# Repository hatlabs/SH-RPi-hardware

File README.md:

# Sailor Hat for Raspberry Pi (SH-RPi)

## Introduction

The Sailor Hat for Raspberry Pi (SH-RPi) is a versatile power management board designed for the Raspberry Pi and similar single-board computers. With the SH-RPi connected, you can create deeply integrated servers that shut down safely when power is turned off and wake up automatically when power is restored.

SH-RPi supports all Raspberry Pi models with a 40-pin GPIO header (every model since the Pi 1 Model B+). Additionally, it is compatible with Raspberry Pi Compute Module 4 boards and other single-board computers that have a 40-pin Raspberry Pi-compatible GPIO header or an external I2C interface with a 5V power input.

The [documentation site](https://docs.hatlabs.fi/sh-rpi/) has details on the hardware and software features of the board.

This repository contains the KiCad hardware design files for Sailor Hat.
There are two other related repositories: 
[firmware](https://github.com/hatlabs/SH-RPi-firmware) and 
[daemon](https://github.com/hatlabs/SH-RPi-daemon).

The documentation site is at [docs.hatlabs.fi/sh-rpi](https://docs.hatlabs.fi/). The devices are available for purchase at [shop.hatlabs.fi](https://shop.hatlabs.fi).

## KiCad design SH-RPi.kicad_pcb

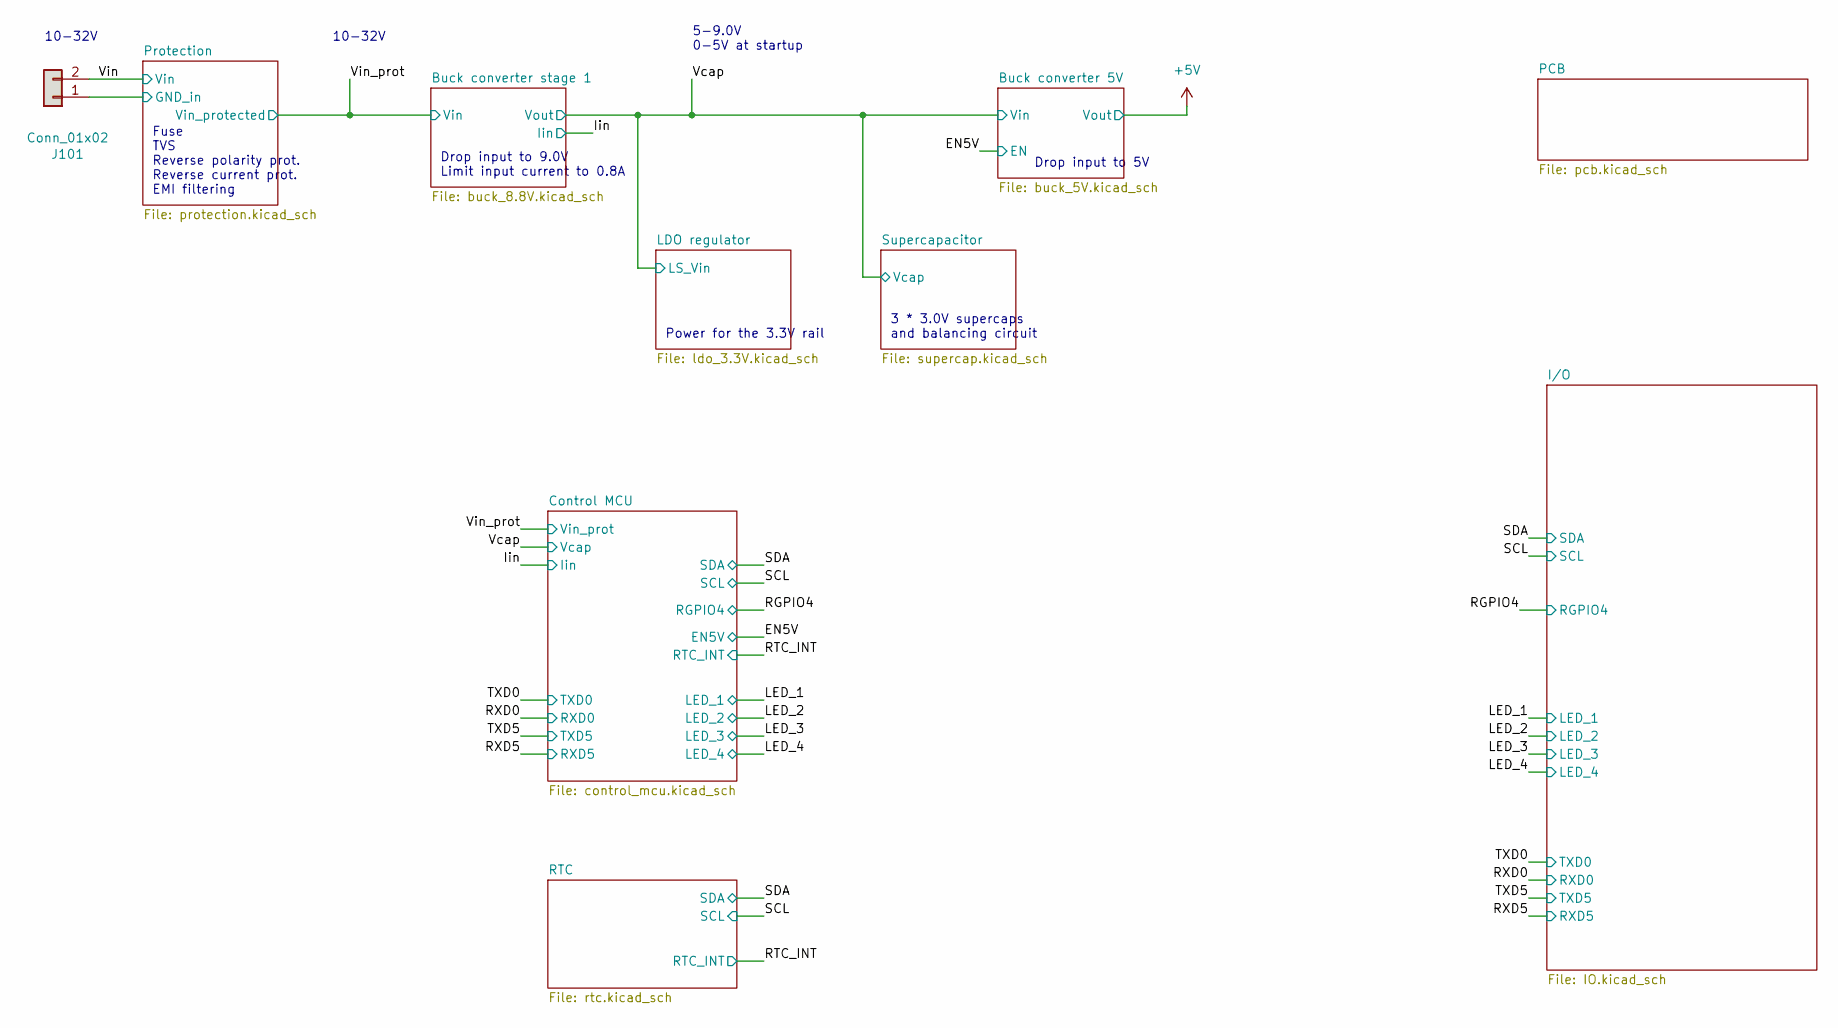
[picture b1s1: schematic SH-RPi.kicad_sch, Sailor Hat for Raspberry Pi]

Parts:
J101: Conn_01x02; PhoenixContact_MC_1,5_2-G-3.81_1x02_P3.81mm_Horizontal; LCSC C8387

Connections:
/Protection/GND_in: J101.1; also elsewhere on the board
/Vin: J101.2; also elsewhere on the board

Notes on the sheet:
Power for the 3.3V rail
Drop input to 5V
3 * 3.0V supercaps and balancing circuit
5-9.0V 0-5V at startup
10-32V
Fuse TVS Reverse polarity prot. Reverse current prot. EMI filtering
Drop input to 9.0V Limit input current to 0.8A

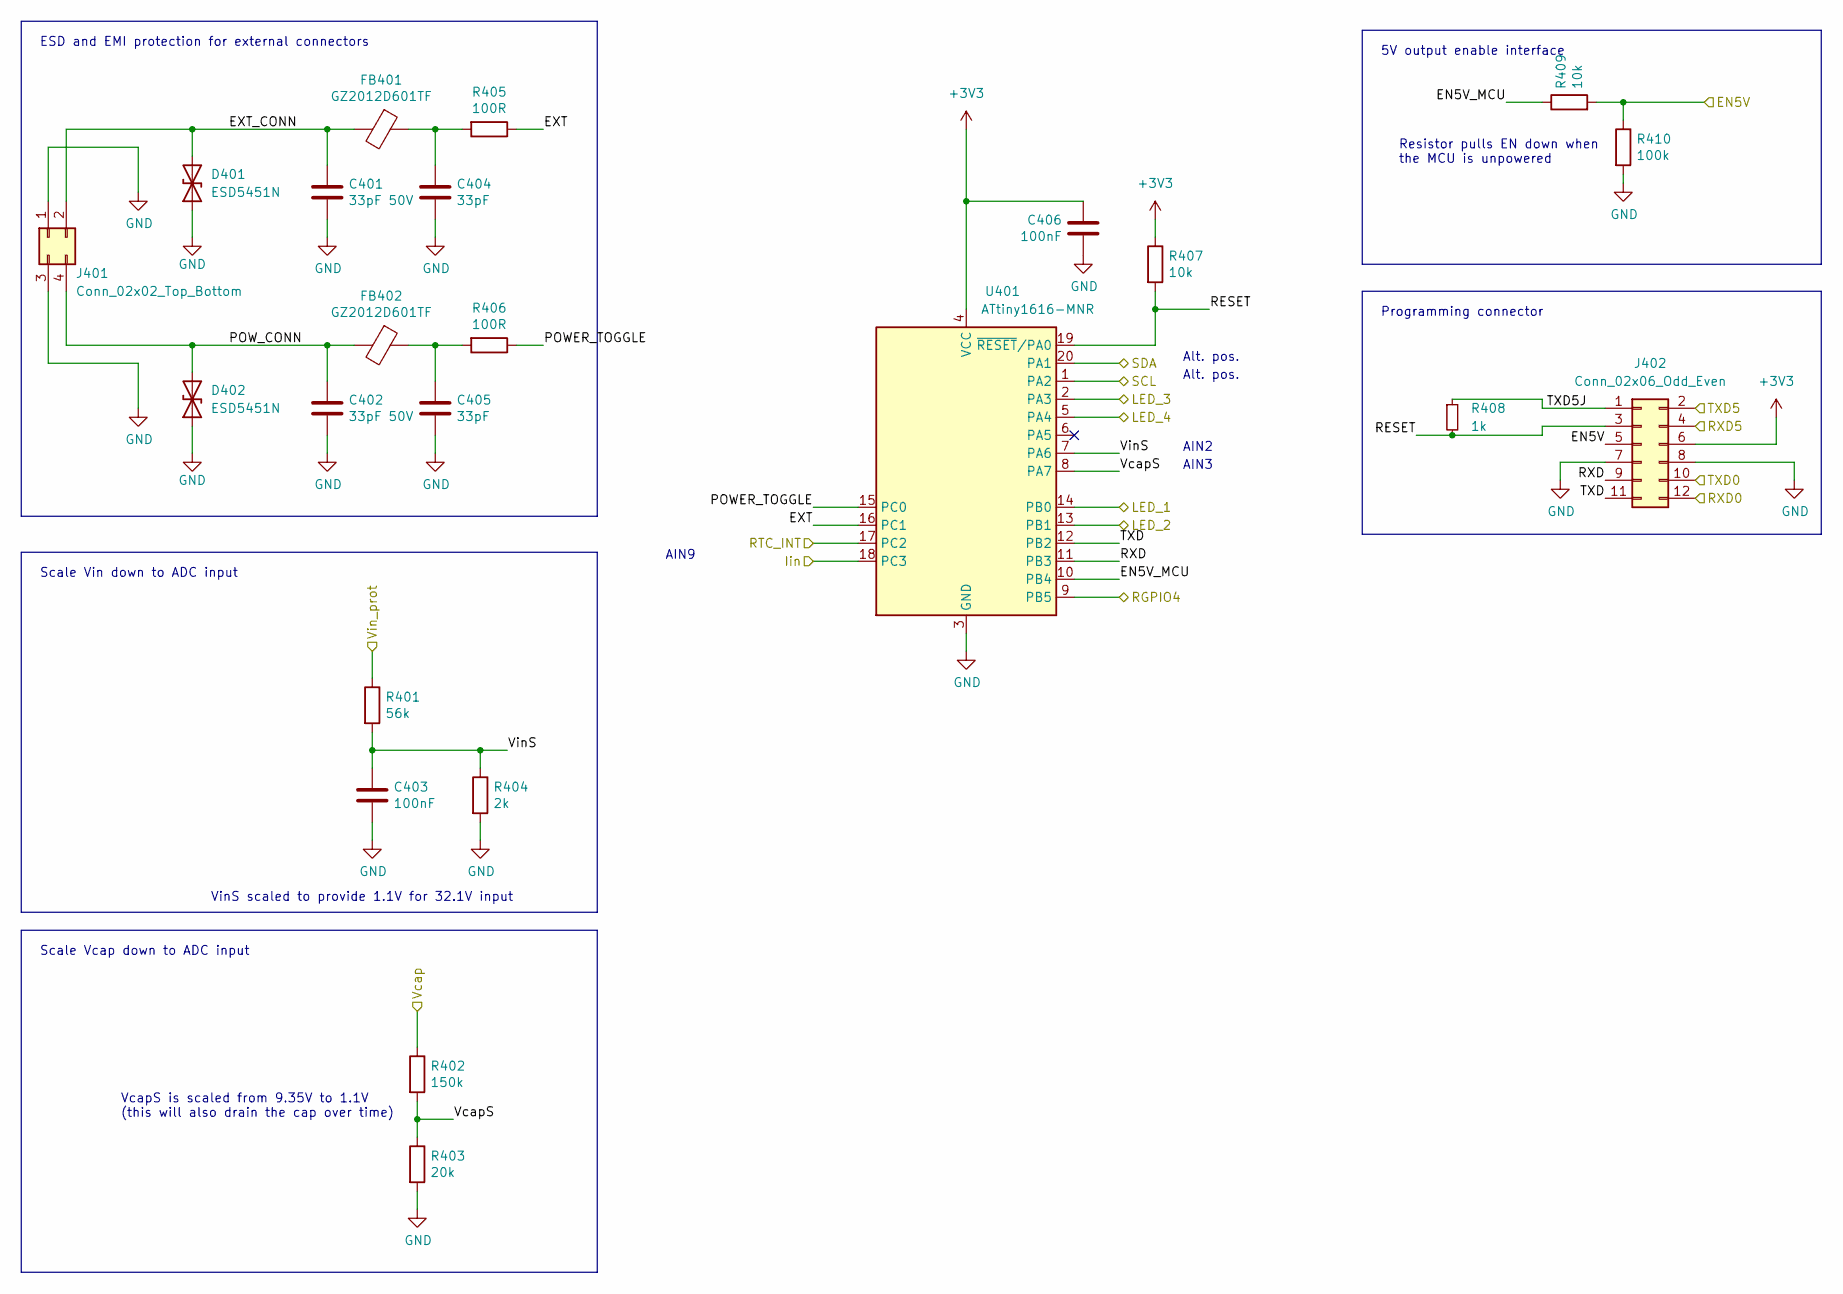
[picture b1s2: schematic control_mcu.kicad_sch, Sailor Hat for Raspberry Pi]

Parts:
C401, C402: 33pF 50V; C_0603_1608Metric; LCSC C1663
C403, C406: 100nF; C_0402_1005Metric; LCSC C1525
C404, C405: 33pF; C_0402_1005Metric; LCSC C1562
D401, D402: ESD5451N; D_0402_1005Metric; LCSC C2936977
FB401, FB402: GZ2012D601TF; L_0805_2012Metric; LCSC C1017
J401: Conn_02x02_Top_Bottom; PinHeader_2x02_P2.54mm_Vertical; LCSC C492419
J402: Conn_02x06_Odd_Even; PinHeader_2x06_P2.54mm_Vertical; LCSC C5383107
R401: 56k; R_0402_1005Metric; LCSC C25796
R402: 150k; R_0402_1005Metric; LCSC C93947
R403: 20k; R_0402_1005Metric; LCSC C25765
R404: 2k; R_0402_1005Metric; LCSC C4109
R405, R406: 100R; R_0402_1005Metric; LCSC C25076
R407, R409: 10k; R_0402_1005Metric; LCSC C25744
R408: 1k; R_0402_1005Metric; LCSC C11702
R410: 100k; R_0402_1005Metric; LCSC C25741
U401: ATtiny1616-MNR; VQFN-20-1EP_3x3mm_P0.4mm_EP1.7x1.7mm; LCSC C507118

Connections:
+3V3: C406.1, J402.6, R407.1, U401.4 (VCC); also elsewhere on the board
/Control MCU/EN5V_MCU: R409.1, U401.10 (PB4)
/Control MCU/EXT: R405.1, U401.16 (PC1)
/Control MCU/EXT_CONN: C401.1, D401.2 (A2), FB401.2, J401.2
/Control MCU/POWER_TOGGLE: R406.1, U401.15 (PC0)
/Control MCU/POW_CONN: C402.1, D402.2 (A2), FB402.2, J401.4
/Control MCU/RESET: J402.3, R407.2, R408.2, U401.19 (~RESET/PA0)
/Control MCU/RXD: J402.9, U401.11 (PB3)
/Control MCU/TXD: J402.11, U401.12 (PB2)
/Control MCU/TXD5J: J402.1, R408.1
/Control MCU/VcapS: R402.2, R403.1, U401.8 (PA7)
/Control MCU/VinS: C403.1, R401.2, R404.1, U401.7 (PA6)
/EN5V: J402.5, R409.2, R410.1; also elsewhere on the board
/Iin: U401.18 (PC3); also elsewhere on the board
/LED_1: U401.14 (PB0); also elsewhere on the board
/LED_2: U401.13 (PB1); also elsewhere on the board
/LED_3: U401.2 (PA3); also elsewhere on the board
/LED_4: U401.5 (PA4); also elsewhere on the board
/RGPIO4: U401.9 (PB5); also elsewhere on the board
/RTC_INT: U401.17 (PC2); also elsewhere on the board
/RXD0: J402.12; also elsewhere on the board
/RXD5: J402.4; also elsewhere on the board
/SCL: U401.1 (PA2); also elsewhere on the board
/SDA: U401.20 (PA1); also elsewhere on the board
/TXD0: J402.10; also elsewhere on the board
/TXD5: J402.2; also elsewhere on the board
/Vcap: R402.1; also elsewhere on the board
/Vin_prot: R401.1; also elsewhere on the board
GND: C401.2, C402.2, C403.2, C404.2, C405.2, C406.2, D401.1 (A1), D402.1 (A1), J401.1, J401.3, J402.7, J402.8, R403.2, R404.2, R410.2, U401.3 (GND), U401.21 (GND); also elsewhere on the board
unnamed: C404.1, FB401.1, R405.2
unnamed: C405.1, FB402.1, R406.2

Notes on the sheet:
Resistor pulls EN down when the MCU is unpowered
AIN2
Scale Vin down to ADC input
Programming connector
Scale Vcap down to ADC input
Alt. pos.
VinS scaled to provide 1.1V for 32.1V input
ESD and EMI protection for external connectors
AIN9
5V output enable interface
AIN3
VcapS is scaled from 9.35V to 1.1V (this will also drain the cap over time)

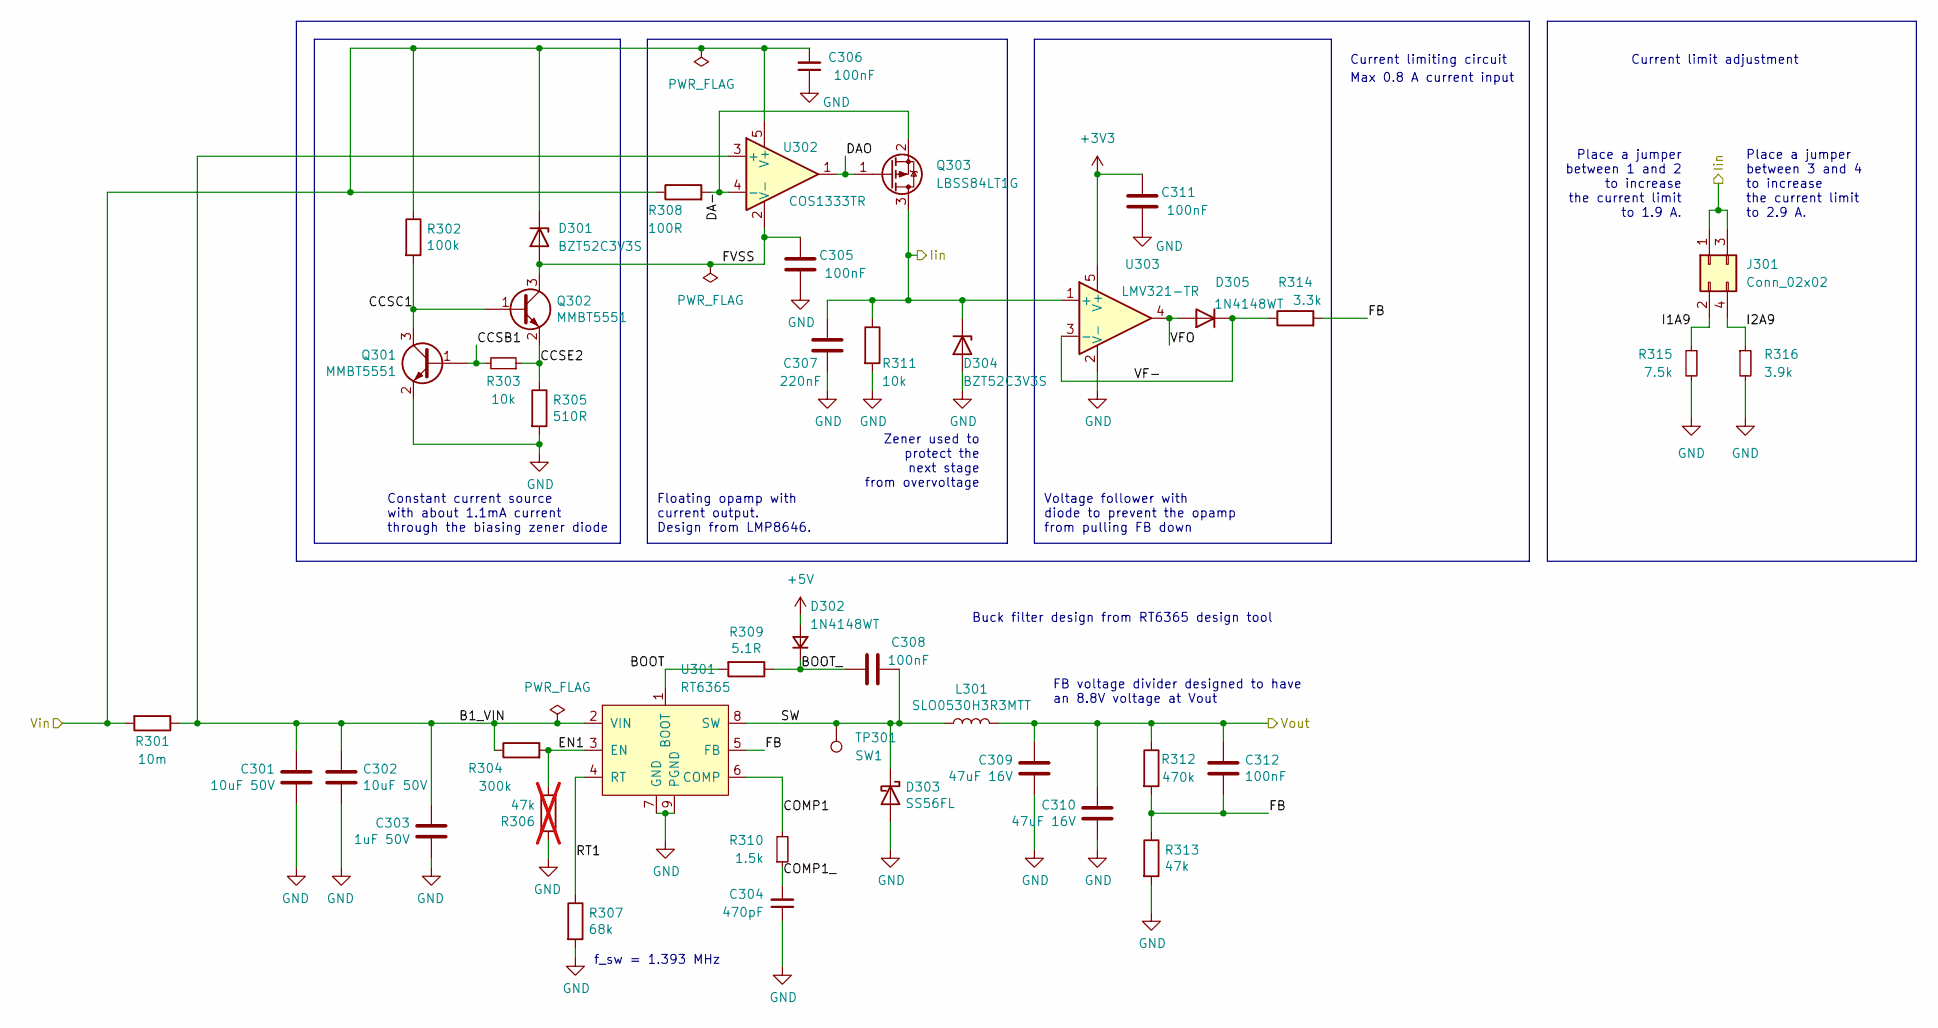
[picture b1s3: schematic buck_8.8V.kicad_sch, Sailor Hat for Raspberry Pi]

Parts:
C301, C302: 10uF 50V; C_1206_3216Metric; LCSC C13585
C303: 1uF 50V; C_0603_1608Metric; LCSC C15849
C304: 470pF; C_0402_1005Metric; LCSC C1537
C305, C306, C311, C312: 100nF; C_0402_1005Metric; LCSC C1525
C307: 220nF; C_0402_1005Metric; LCSC C16772
C308: 100nF; C_0603_1608Metric; LCSC C14663
C309, C310: 47uF 16V; C_1210_3225Metric; LCSC C77101
D301, D304: BZT52C3V3S; D_SOD-323; LCSC C173439
D302, D305: 1N4148WT; D_SOD-523; LCSC C414017
D303: SS56FL; D_SMA; LCSC C122865
J301: Conn_02x02; PinHeader_2x02_P2.54mm_Vertical; LCSC C492419
L301: SLO0530H3R3MTT; L_MWSA0503S; LCSC C325963
Q301, Q302: MMBT5551; SOT-23; LCSC C2145
Q303: LBSS84LT1G; SOT-23; LCSC C8492
R301: 10m; R_1206_3216Metric; LCSC C105362
R302: 100k; R_0402_1005Metric; LCSC C25741
R303, R311: 10k; R_0402_1005Metric; LCSC C25744
R304: 300k; R_0402_1005Metric; LCSC C25774
R305: 510R; R_0402_1005Metric; LCSC C25123
R306: 47k; R_0402_1005Metric; LCSC C25792; not fitted
R307: 68k; R_0402_1005Metric; LCSC C137947
R308: 100R; R_0402_1005Metric; LCSC C25076
R309: 5.1R; R_0603_1608Metric; LCSC C25197
R310: 1.5k; R_0402_1005Metric; LCSC C25867
R312: 470k; R_0402_1005Metric; LCSC C137976
R313: 47k; R_0402_1005Metric; LCSC C25792
R314: 3.3k; R_0402_1005Metric; LCSC C25890
R315: 7.5k; R_0402_1005Metric; LCSC C137934
R316: 3.9k; R_0402_1005Metric; LCSC C131467
TP301: SW1; TestPoint_Pad_D2.0mm
U301: RT6365; SOIC-8-1EP_3.9x4.9mm_P1.27mm_EP2.41x3.3mm_ThermalVias; LCSC C3024482
U302: COS1333TR; SOT-23-5; LCSC C693072
U303: LMV321-TR; SOT-23-5; LCSC C3014306

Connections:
+3V3: C311.2, U303.5 (V+); also elsewhere on the board
+5V: D302.2 (A); also elsewhere on the board
/Buck converter stage 1/B1_VIN: C301.1, C302.1, C303.1, R301.1, R304.1, U301.2 (VIN), U302.3 (+)
/Buck converter stage 1/BOOT: R309.2, U301.1 (BOOT)
/Buck converter stage 1/BOOT_: C308.2, D302.1 (K), R309.1
/Buck converter stage 1/CCSB1: Q301.1 (B), R303.2
/Buck converter stage 1/CCSC1: Q301.3 (C), Q302.1 (B), R302.2
/Buck converter stage 1/CCSE2: Q302.2 (E), R303.1, R305.1
/Buck converter stage 1/COMP1: R310.2, U301.6 (COMP)
/Buck converter stage 1/COMP1_: C304.2, R310.1
/Buck converter stage 1/DA-: Q303.2 (S), R308.2, U302.4 (-)
/Buck converter stage 1/DAO: Q303.1 (G), U302.1
/Buck converter stage 1/EN1: R304.2, R306.2, U301.3 (EN)
/Buck converter stage 1/FB: C312.2, R312.2, R313.1, R314.2, U301.5 (FB)
/Buck converter stage 1/FVSS: C305.2, D301.2 (A), Q302.3 (C), U302.2 (V-)
/Buck converter stage 1/I1A9: J301.2, R315.1
/Buck converter stage 1/I2A9: J301.4, R316.1
/Buck converter stage 1/RT1: R307.1, U301.4 (RT)
/Buck converter stage 1/SW: C308.1, D303.1 (K), L301.1, TP301.1 (1_1), U301.8 (SW)
/Buck converter stage 1/VF-: D305.1 (K), R314.1, U303.3 (-)
/Buck converter stage 1/VFO: D305.2 (A), U303.4
/Iin: C307.2, D304.1 (K), J301.1, J301.3, Q303.3 (D), R311.1, U303.1 (+); also elsewhere on the board
/Vcap: C309.1, C310.1, C312.1, L301.2, R312.1; also elsewhere on the board
/Vin_prot: C306.2, D301.1 (K), R301.2, R302.1, R308.1, U302.5 (V+); also elsewhere on the board
GND: C301.2, C302.2, C303.2, C304.1, C305.1, C306.1, C307.1, C309.2, C310.2, C311.1, D303.2 (A), D304.2 (A), Q301.2 (E), R305.2, R306.1, R307.2, R311.2, R313.2, R315.2, R316.2, U301.7 (GND), U301.9 (PGND), U303.2 (V-); also elsewhere on the board

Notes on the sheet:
Voltage follower with diode to prevent the opamp from pulling FB down
Constant current source with about 1.1mA current through the biasing zener diode
f_sw = 1.393 MHz
Place a jumper between 1 and 2 to increase the current limit to 1.9 A.
Place a jumper between 3 and 4 to increase the current limit to 2.9 A.
Zener used to protect the next stage from overvoltage
FB voltage divider designed to have an 8.8V voltage at Vout
Buck filter design from RT6365 design tool
Max 0.8 A current input
Current limit adjustment
Floating opamp with current output. Design from LMP8646.
Current limiting circuit

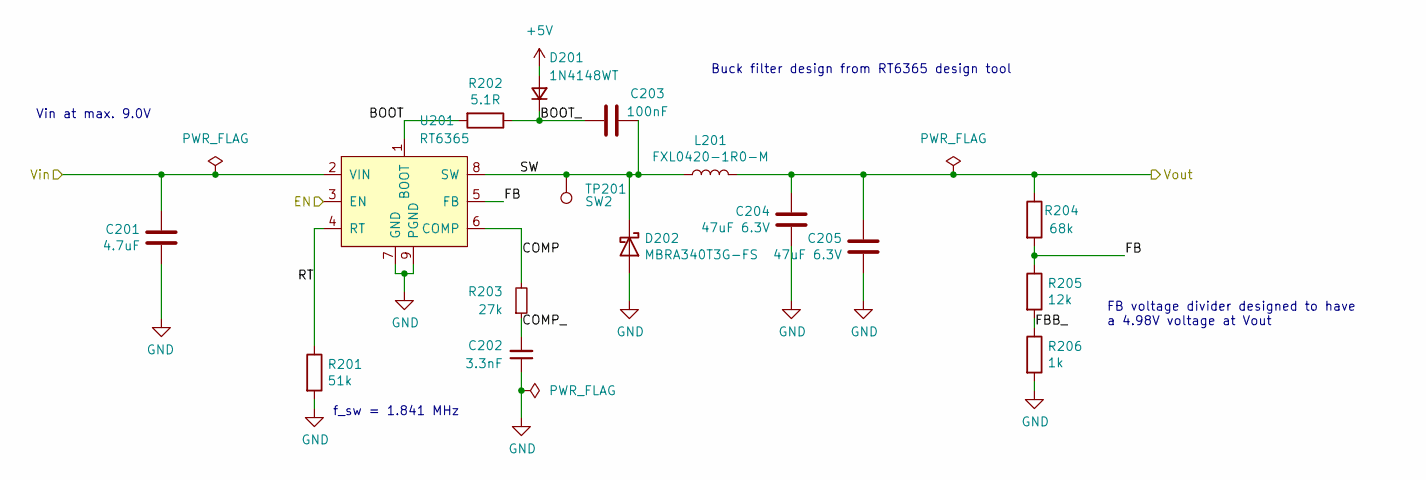
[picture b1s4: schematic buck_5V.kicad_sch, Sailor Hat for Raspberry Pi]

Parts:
C201: 4.7uF; C_0603_1608Metric; LCSC C19666
C202: 3.3nF; C_0402_1005Metric; LCSC C26404
C203: 100nF; C_0603_1608Metric; LCSC C14663
C204, C205: 47uF 6.3V; C_1210_3225Metric; LCSC C77101
D201: 1N4148WT; D_SOD-523; LCSC C414017
D202: MBRA340T3G-FS; D_SMA; LCSC C5563736
L201: FXL0420-1R0-M; L_MWSA0402; LCSC C167203
R201: 51k; R_0402_1005Metric; LCSC C25794
R202: 5.1R; R_0603_1608Metric; LCSC C25197
R203: 27k; R_0402_1005Metric; LCSC C25771
R204: 68k; R_0402_1005Metric; LCSC C137947
R205: 12k; R_0402_1005Metric; LCSC C25752
R206: 1k; R_0402_1005Metric; LCSC C11702
TP201: SW2; TestPoint_Pad_D2.0mm
U201: RT6365; SOIC-8-1EP_3.9x4.9mm_P1.27mm_EP2.41x3.3mm_ThermalVias; LCSC C3024482

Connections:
+5V: C204.1, C205.1, D201.2 (A), L201.2, R204.1; also elsewhere on the board
/Buck converter 5V/BOOT: R202.2, U201.1 (BOOT)
/Buck converter 5V/BOOT_: C203.2, D201.1 (K), R202.1
/Buck converter 5V/COMP: R203.2, U201.6 (COMP)
/Buck converter 5V/COMP_: C202.2, R203.1
/Buck converter 5V/FB: R204.2, R205.1, U201.5 (FB)
/Buck converter 5V/FBB_: R205.2, R206.1
/Buck converter 5V/RT: R201.1, U201.4 (RT)
/Buck converter 5V/SW: C203.1, D202.1 (K), L201.1, TP201.1 (1_1), U201.8 (SW)
/EN5V: U201.3 (EN); also elsewhere on the board
/Vcap: C201.1, U201.2 (VIN); also elsewhere on the board
GND: C201.2, C202.1, C204.2, C205.2, D202.2 (A), R201.2, R206.2, U201.7 (GND), U201.9 (PGND); also elsewhere on the board

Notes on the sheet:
FB voltage divider designed to have a 4.98V voltage at Vout
Vin at max. 9.0V
Buck filter design from RT6365 design tool
f_sw = 1.841 MHz

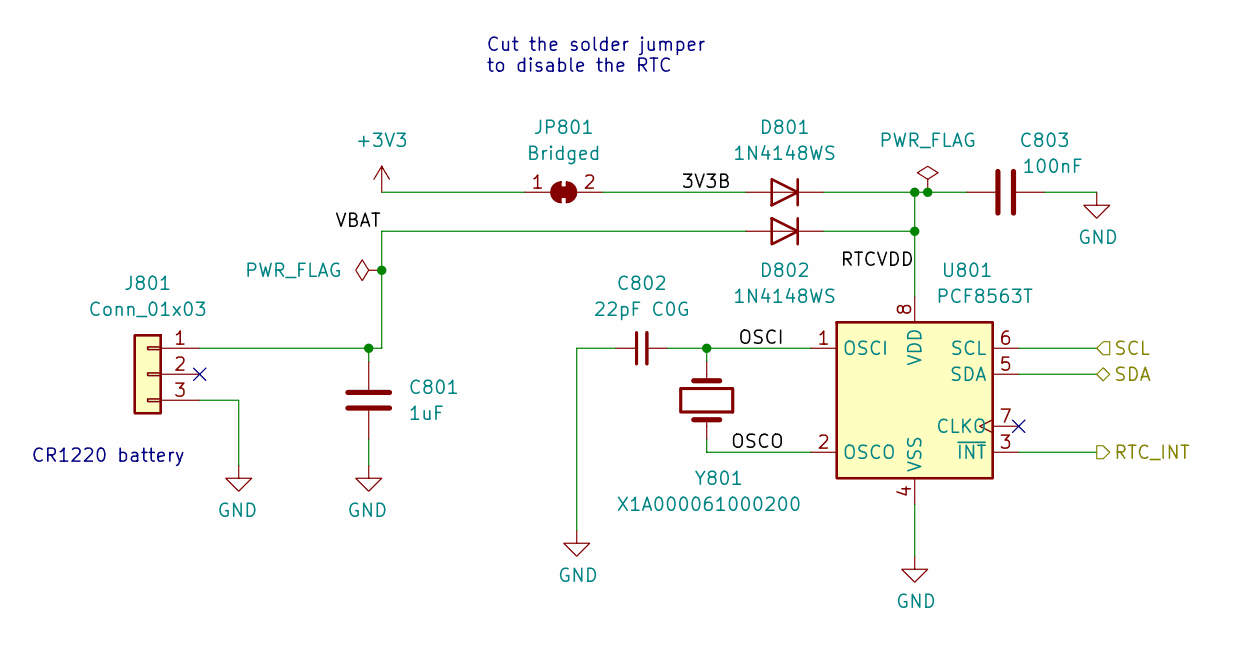
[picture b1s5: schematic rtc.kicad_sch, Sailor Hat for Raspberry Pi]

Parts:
C801: 1uF; C_0402_1005Metric; LCSC C52923
C802: 22pF C0G; C_0603_1608Metric; LCSC C1653
C803: 100nF; C_0402_1005Metric; LCSC C1525
D801, D802: 1N4148WS; D_SOD-323; LCSC C2128
J801: Conn_01x03; BatteryHolder_Myoung_MY-1220-03; LCSC C964818
JP801: Bridged; SolderJumper-2_P1.3mm_Bridged2Bar_Pad1.0x1.5mm
U801: PCF8563T; SOIC-8_3.9x4.9mm_P1.27mm; LCSC C7440
Y801: X1A000061000200; Crystal_SMD_2012-2Pin_2.0x1.2mm; LCSC C55208

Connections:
+3V3: JP801.1 (A); also elsewhere on the board
/RTC/3V3B: D801.2 (A), JP801.2 (B)
/RTC/OSCI: C802.2, U801.1 (OSCI), Y801.2
/RTC/OSCO: U801.2 (OSCO), Y801.1
/RTC/RTCVDD: C803.1, D801.1 (K), D802.1 (K), U801.8 (VDD)
/RTC/VBAT: C801.1, D802.2 (A), J801.1
/RTC_INT: U801.3 (~INT); also elsewhere on the board
/SCL: U801.6 (SCL); also elsewhere on the board
/SDA: U801.5 (SDA); also elsewhere on the board
GND: C801.2, C802.1, C803.2, J801.3, U801.4 (VSS); also elsewhere on the board

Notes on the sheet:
Cut the solder jumper to disable the RTC
CR1220 battery

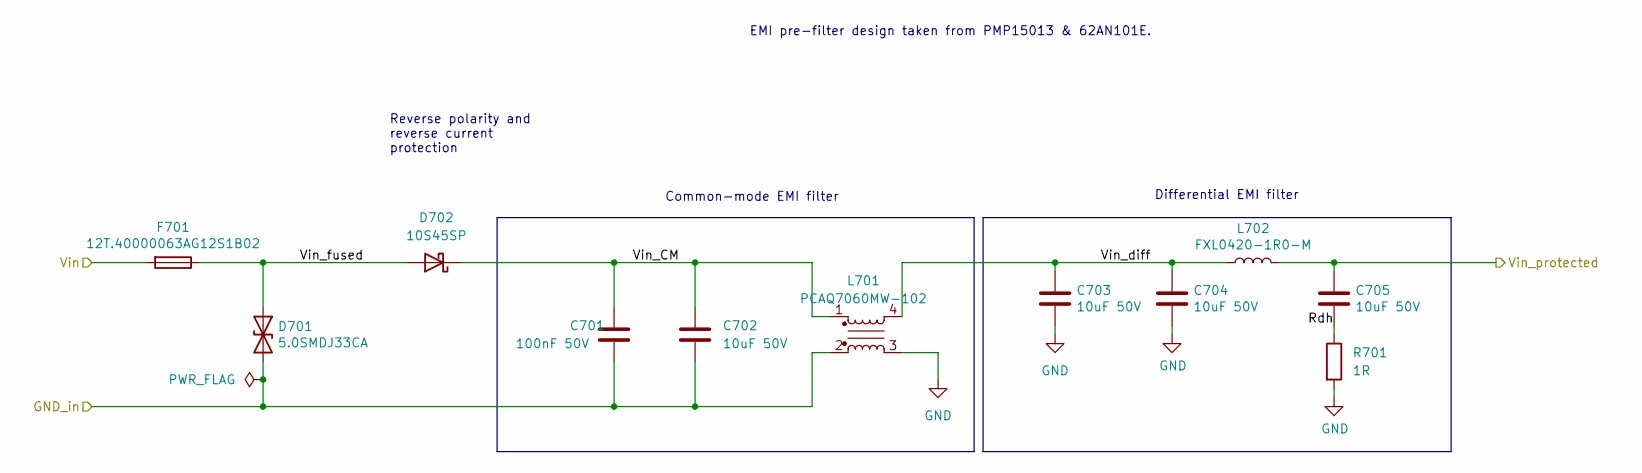
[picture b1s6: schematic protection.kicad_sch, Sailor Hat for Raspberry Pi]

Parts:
C701: 100nF 50V; C_0603_1608Metric; LCSC C14663
C702, C703, C704, C705: 10uF 50V; C_1206_3216Metric; LCSC C13585
D701: 5.0SMDJ33CA; D_SMC; LCSC C2913642
D702: 10S45SP; SS5U100_TO-277; LCSC C2988031
F701: 12T.40000063AG12S1B02; Fuse_1206_3216Metric; LCSC C140479
L701: PCAQ7060MW-102; L_CMF7060F; LCSC C2915648
L702: FXL0420-1R0-M; L_MWSA0402; LCSC C167203
R701: 1R; C_0603_1608Metric; LCSC C22936

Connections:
/Protection/GND_in: C701.2, C702.2, D701.2 (A2), L701.2; also elsewhere on the board
/Protection/Rdh: C705.2, R701.1
/Protection/Vin_CM: C701.1, C702.1, D702.1 (K), L701.1
/Protection/Vin_diff: C703.1, C704.1, L701.4, L702.1
/Protection/Vin_fused: D701.1 (A1), D702.2 (A), F701.1
/Vin: F701.2; also elsewhere on the board
/Vin_prot: C705.1, L702.2; also elsewhere on the board
GND: C703.2, C704.2, L701.3, R701.2; also elsewhere on the board

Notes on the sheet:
Reverse polarity and reverse current protection
EMI pre-filter design taken from PMP15013 & 62AN101E.
Differential EMI filter
Common-mode EMI filter

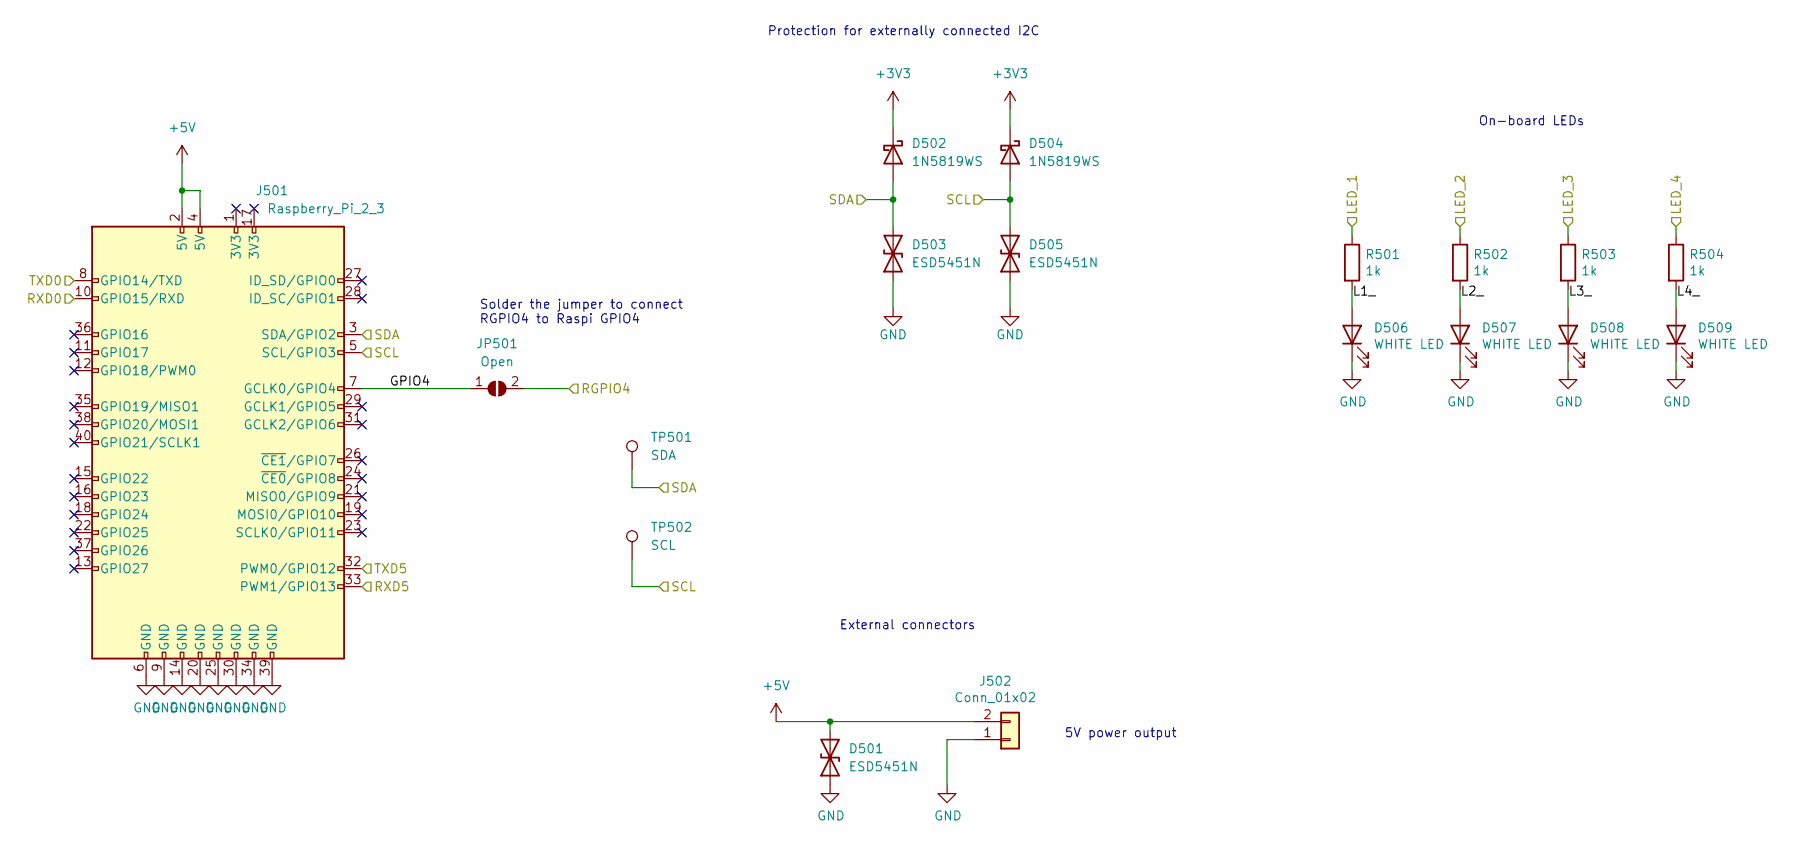
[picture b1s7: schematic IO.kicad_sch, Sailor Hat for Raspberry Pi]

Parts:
D501, D503, D505: ESD5451N; D_0402_1005Metric; LCSC C2936977
D502, D504: 1N5819WS; D_SOD-323_HandSoldering; LCSC C191023
D506, D507, D508, D509: WHITE LED; LED_0603_1608Metric; LCSC C434422
J501: Raspberry_Pi_2_3; PassthroughPinSocket_FH-00339_2x40_P2.54mm_Vertical_Bottom; LCSC C2685112
J502: Conn_01x02; CONN-TH_2P-P2.54_CONN-TH_2P-P2.54_; LCSC C2927503
JP501: Open; SolderJumper-2_P1.3mm_Open_TrianglePad1.0x1.5mm
R501, R502, R503, R504: 1k; R_0402_1005Metric; LCSC C11702
TP501: SDA; TestPoint_Pad_D2.0mm
TP502: SCL; TestPoint_Pad_D2.0mm

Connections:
+3V3: D502.1 (K), D504.1 (K); also elsewhere on the board
+5V: D501.2 (A2), J501.2 (5V), J501.4 (5V), J502.2; also elsewhere on the board
/I/O/GPIO4: J501.7 (GCLK0/GPIO4), JP501.1 (A)
/I/O/L1_: D506.2 (A), R501.2
/I/O/L2_: D507.2 (A), R502.2
/I/O/L3_: D508.2 (A), R503.2
/I/O/L4_: D509.2 (A), R504.2
/LED_1: R501.1; also elsewhere on the board
/LED_2: R502.1; also elsewhere on the board
/LED_3: R503.1; also elsewhere on the board
/LED_4: R504.1; also elsewhere on the board
/RGPIO4: JP501.2 (B); also elsewhere on the board
/RXD0: J501.10 (GPIO15/RXD); also elsewhere on the board
/RXD5: J501.33 (PWM1/GPIO13); also elsewhere on the board
/SCL: D504.2 (A), D505.2 (A2), J501.5 (SCL/GPIO3), TP502.1 (1_1); also elsewhere on the board
/SDA: D502.2 (A), D503.2 (A2), J501.3 (SDA/GPIO2), TP501.1 (1_1); also elsewhere on the board
/TXD0: J501.8 (GPIO14/TXD); also elsewhere on the board
/TXD5: J501.32 (PWM0/GPIO12); also elsewhere on the board
GND: D501.1 (A1), D503.1 (A1), D505.1 (A1), D506.1 (K), D507.1 (K), D508.1 (K), D509.1 (K), J501.6 (GND), J501.9 (GND), J501.14 (GND), J501.20 (GND), J501.25 (GND), J501.30 (GND), J501.34 (GND), J501.39 (GND), J502.1; also elsewhere on the board

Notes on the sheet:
On-board LEDs
Protection for externally connected I2C
External connectors
5V power output
Solder the jumper to connect RGPIO4 to Raspi GPIO4

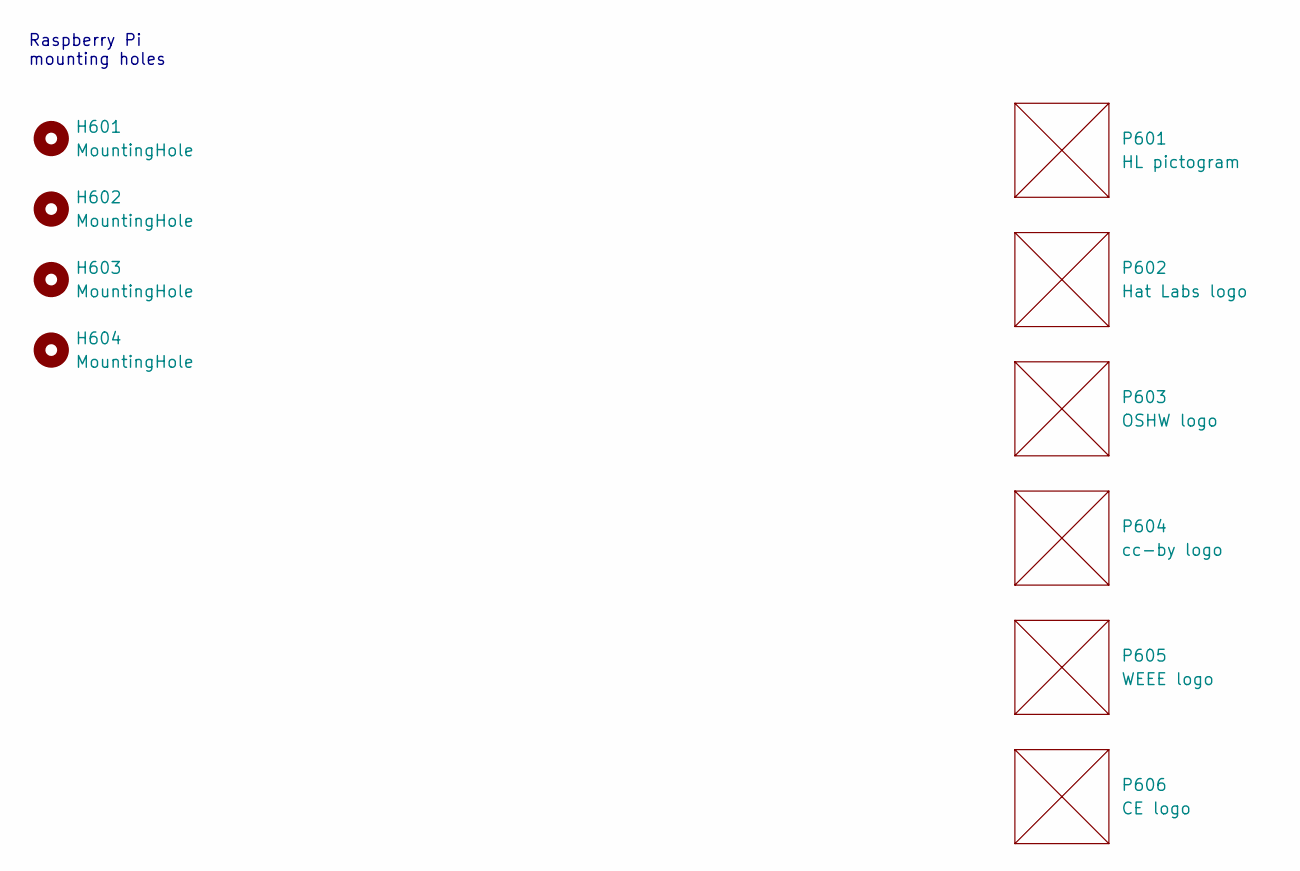
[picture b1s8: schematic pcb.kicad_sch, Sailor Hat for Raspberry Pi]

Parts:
H601, H602, H603, H604: MountingHole; MountingHole_Pi_2.75mm_M2.5
P601: HL pictogram; HL_pictogram_6.3mm
P602: Hat Labs logo; Hat_Labs_25.4mm
P603: OSHW logo; OSHW-Logo_11.4x12mm_SilkScreen
P604: cc-by logo; cc-by_5mm
P605: WEEE logo; WEEE-Logo_4.2x6mm_SilkScreen
P606: CE logo; CE-Logo_8.5x6mm_SilkScreen

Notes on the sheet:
Raspberry Pi mounting holes

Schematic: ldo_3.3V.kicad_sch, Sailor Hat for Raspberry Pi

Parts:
C901: 1uF 16V; C_0402_1005Metric; LCSC C52923
C902: 10uF 6.3V; C_0402_1005Metric; LCSC C15525
D901: 1N5819WS; D_SOD-323_HandSoldering; LCSC C191023
TP901: 3V3; TestPoint_Pad_D2.0mm
U901: HT7533-1; SOT-23; LCSC C5279052

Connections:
+3V3: C902.1, TP901.1 (1_1), U901.2 (VOUT); also elsewhere on the board
/LDO regulator/LDO_in: C901.1, D901.1 (K), U901.3 (VIN)
/Vcap: D901.2 (A); also elsewhere on the board
GND: C901.2, C902.2, U901.1 (GND); also elsewhere on the board

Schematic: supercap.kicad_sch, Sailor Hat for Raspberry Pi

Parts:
C1001, C1002, C1003: 100nF; C_0402_1005Metric; LCSC C1525
C1004, C1005, C1006: CAS SCAP 3.0V20F; CP_Radial_D12.6mm_H26.0mm_P5.30mm_Horizontal; JLCPCB_IGNORE 1
D1001, D1002, D1003: 1N5819WS; D_SOD-323_HandSoldering; LCSC C191023
Q1001, Q1002, Q1003: SS8050; SOT-23; LCSC C2150
R1001, R1002, R1003: 33k; R_0402_1005Metric; LCSC C25779
R1004, R1007, R1010, R1014, R1016, R1018: 300k; R_0402_1005Metric; LCSC C25774
R1005, R1008, R1011: 150k; R_0402_1005Metric; LCSC C93947
R1006, R1009, R1012: 120k; R_0402_1005Metric; LCSC C93945
R1013, R1015, R1017: 330k; R_0402_1005Metric; LCSC C25778
U1001, U1002, U1003: LMV321-TR; SOT-23-5; LCSC C3014306

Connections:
/Supercapacitor/BO1+: R1010.2, R1011.1, U1003.1 (+)
/Supercapacitor/BO1+_: R1011.2, R1012.1
/Supercapacitor/BO1-: R1017.2, R1018.1, U1003.3 (-)
/Supercapacitor/BO1o: Q1003.1 (B), U1003.4
/Supercapacitor/BO2+: R1007.2, R1008.1, U1002.1 (+)
/Supercapacitor/BO2+_: R1008.2, R1009.1
/Supercapacitor/BO2-: R1015.2, R1016.1, U1002.3 (-)
/Supercapacitor/BO2o: Q1002.1 (B), U1002.4
/Supercapacitor/BO3+: R1004.2, R1005.1, U1001.1 (+)
/Supercapacitor/BO3+_: R1005.2, R1006.1
/Supercapacitor/BO3-: R1013.2, R1014.1, U1001.3 (-)
/Supercapacitor/BO3o: Q1001.1 (B), U1001.4
/Supercapacitor/SC12: C1002.2, C1003.1, C1005.2, C1006.1, D1002.2 (A), D1003.1 (K), Q1002.2 (E), Q1003.3 (C), R1010.1, R1016.2, U1002.2 (V-), U1003.5 (V+)
/Supercapacitor/SC12R: R1002.2, R1003.1, R1009.2, R1017.1
/Supercapacitor/SC23: C1001.2, C1002.1, C1004.2, C1005.1, D1001.2 (A), D1002.1 (K), Q1001.2 (E), Q1002.3 (C), R1007.1, R1014.2, U1001.2 (V-), U1002.5 (V+)
/Supercapacitor/SC23R: R1001.2, R1002.1, R1006.2, R1015.1
/Vcap: C1001.1, C1004.1, D1001.1 (K), Q1001.3 (C), R1001.1, R1004.1, R1013.1, U1001.5 (V+); also elsewhere on the board
GND: C1003.2, C1006.2, D1003.2 (A), Q1003.2 (E), R1003.2, R1012.2, R1018.2, U1003.2 (V-); also elsewhere on the board

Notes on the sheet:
Balancing circuit modeled after https://www.eevblog.com/forum/renewable-energy/supercapacitor-balancer/

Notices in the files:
IO.kicad_sch:
https://creativecommons.org/licenses/by/4.0
Sailor Hat for Raspberry Pi is licensed under CC BY 4.0.
sailor-hat.kicad_pcb:
Sailor Hat for ESP32 is licensed under CC BY-SA 4.0.
